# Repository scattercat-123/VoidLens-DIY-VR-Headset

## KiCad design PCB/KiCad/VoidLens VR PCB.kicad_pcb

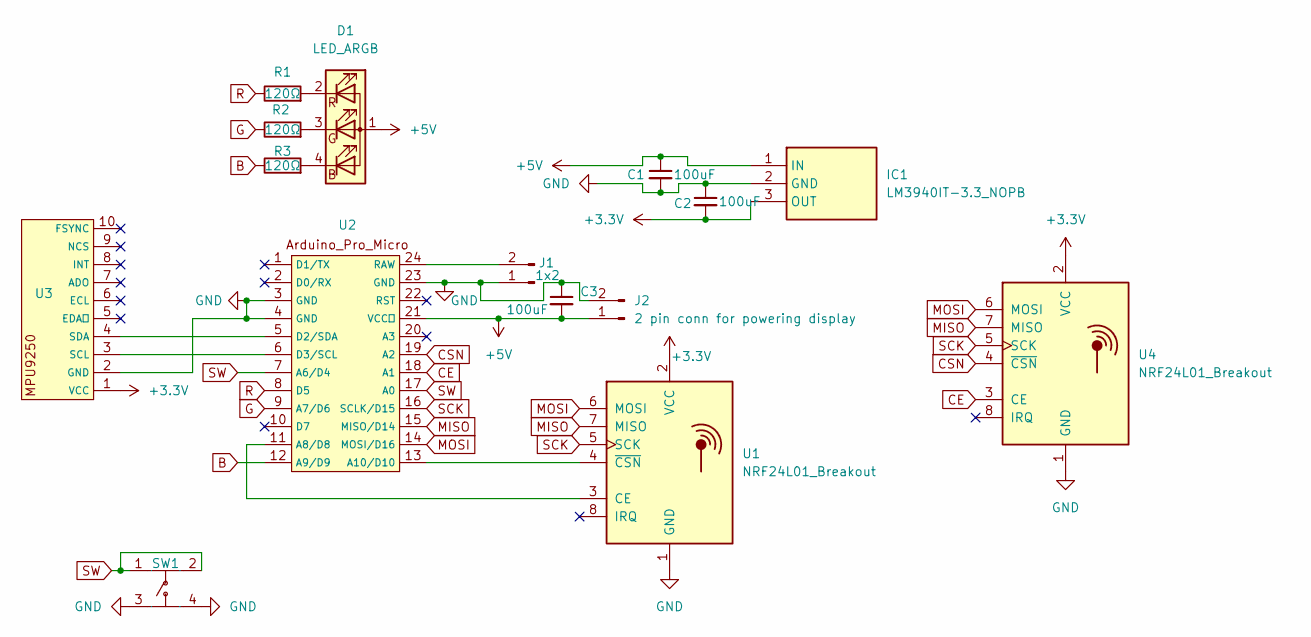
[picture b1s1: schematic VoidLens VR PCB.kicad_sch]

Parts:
C1, C2, C3: 100uF; CP_EIA-3216-18_Kemet-A
D1: LED_ARGB; LED_D5.0mm-4_RGB
IC1: LM3940IT-3.3_NOPB; TO-220-3_Horizontal_TabDown; Manufacturer_Part_Number LM3940IT-3.3/NOPB; Mouser Part Number 926-LM3940IT-3.3NOPB
J1: 1x2; PinHeader_1x02_P2.54mm_Vertical
J2: 2 pin conn for powering display; TestPoint_2Pads_Pitch2.54mm_Drill0.8mm
R1, R2, R3: 120Ω; R_1210_3225Metric
SW1: SW-SMD_4P-L6.2-W6.2-P4.50-LS8.6; Manufacturer Part K2-1157SP-I4SW-01; LCSC Part Name 6.4x6.2x3.7红柄开关
U1, U4: NRF24L01_Breakout; nRF24L01_Breakout
U2: Arduino_Pro_Micro (sparkfun pro micro)
U3: PinHeader_1x10_P2.54mm_Vertical

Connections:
+3.3V: C2.2, IC1.3 (OUT), U1.2 (VCC), U3.1 (VCC), U4.2 (VCC)
+5V: C1.1, C3.2, D1.1 (A), IC1.1 (IN), J2.1, U2.21 (VCC)
B: R3.1, U2.12 (A9/D9)
CE: U2.18 (A1), U4.3 (CE)
CSN: U2.19 (A2), U4.4 (~CSN)
G: R2.1, U2.9 (A7/D6)
GND: C1.2, C2.1, C3.1, IC1.2 (GND), J1.1, J2.2, SW1.3, SW1.4, U1.1 (GND), U2.3 (GND), U2.4 (GND), U2.23 (GND), U3.2 (GND), U4.1 (GND)
MISO: U1.7 (MISO), U2.15 (MISO/D14), U4.7 (MISO)
MOSI: U1.6 (MOSI), U2.14 (MOSI/D16), U4.6 (MOSI)
unnamed: D1.4 (BK), R3.2
unnamed: D1.3 (GK), R2.2
unnamed: D1.2 (RK), R1.2
unnamed: J1.2, U2.24 (RAW)
unnamed: U1.3 (CE), U2.11 (A8/D8)
unnamed: U1.4 (~CSN), U2.13 (A10/D10)
unnamed: U2.5 (D2/SDA), U3.4 (SDA)
unnamed: U2.6 (D3/SCL), U3.3 (SCL)
R: R1.1, U2.8 (D5)
SCK: U1.5 (SCK), U2.16 (SCLK/D15), U4.5 (SCK)
SW: SW1.1, SW1.2, U2.7 (A6/D4), U2.17 (A0)

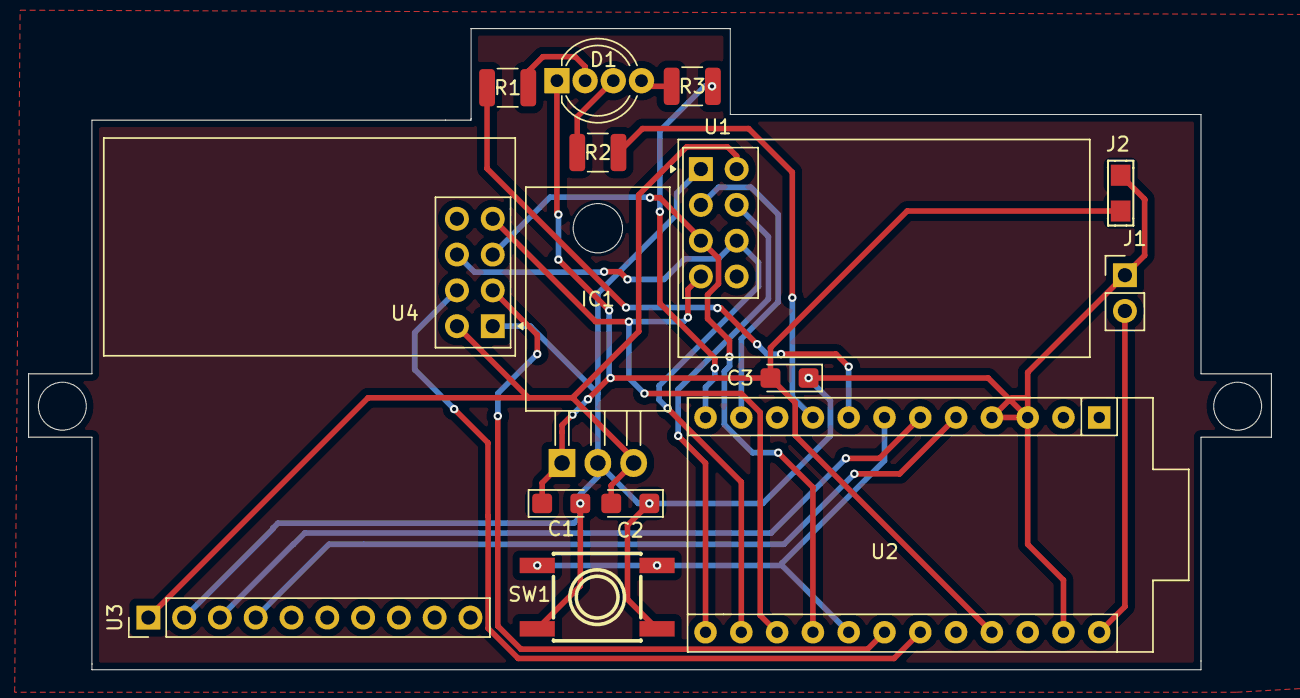
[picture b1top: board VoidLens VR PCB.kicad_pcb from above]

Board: 2 copper layers, 88.2 x 45.5 mm, 15 parts (0 on the bottom side), 20 nets.

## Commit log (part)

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2025-07-30 Created the journal
2025-07-30 updated the readme! make sure to check the journal!
2025-07-30 finished the journal after an hour bruhhhhh
2025-07-30 read b4 checking cad
2025-07-30 added voidlens step file
2025-07-30 Added bom
    https://docs.google.com/spreadsheets/d/1Kba30zyyhuXqx5iu_ySOgdJd4Grd3c3JvfDCplCfUi8/edit?usp=sharing
    online view
2025-07-30 renamed it!
2025-07-30 if you need to see bom online
2025-07-30 renamed
2025-07-30 added f3z format of cad
2025-07-30 added pcb folder
2025-07-30 added the kicad files
2025-07-30 added manufacturing files for pcb
2025-07-30 added all kicad files including pcb step
2025-08-07 adde q and a thx alex
2025-08-07 added q and a
2025-08-15 aded bom to readme
2025-08-15 added hours to journal
2026-05-26 Basic cad
2026-05-28 Add journal entry for VoidLens DIY VR headset revision
    Documented the design process and improvements for the VoidLens DIY VR headset, including CAD work and adjustments for modularity and comfort.
2026-05-29 Revise journal entries for May 28th and 29th
    Updated journal entries with details on CAD work, PCB design, and battery research.
